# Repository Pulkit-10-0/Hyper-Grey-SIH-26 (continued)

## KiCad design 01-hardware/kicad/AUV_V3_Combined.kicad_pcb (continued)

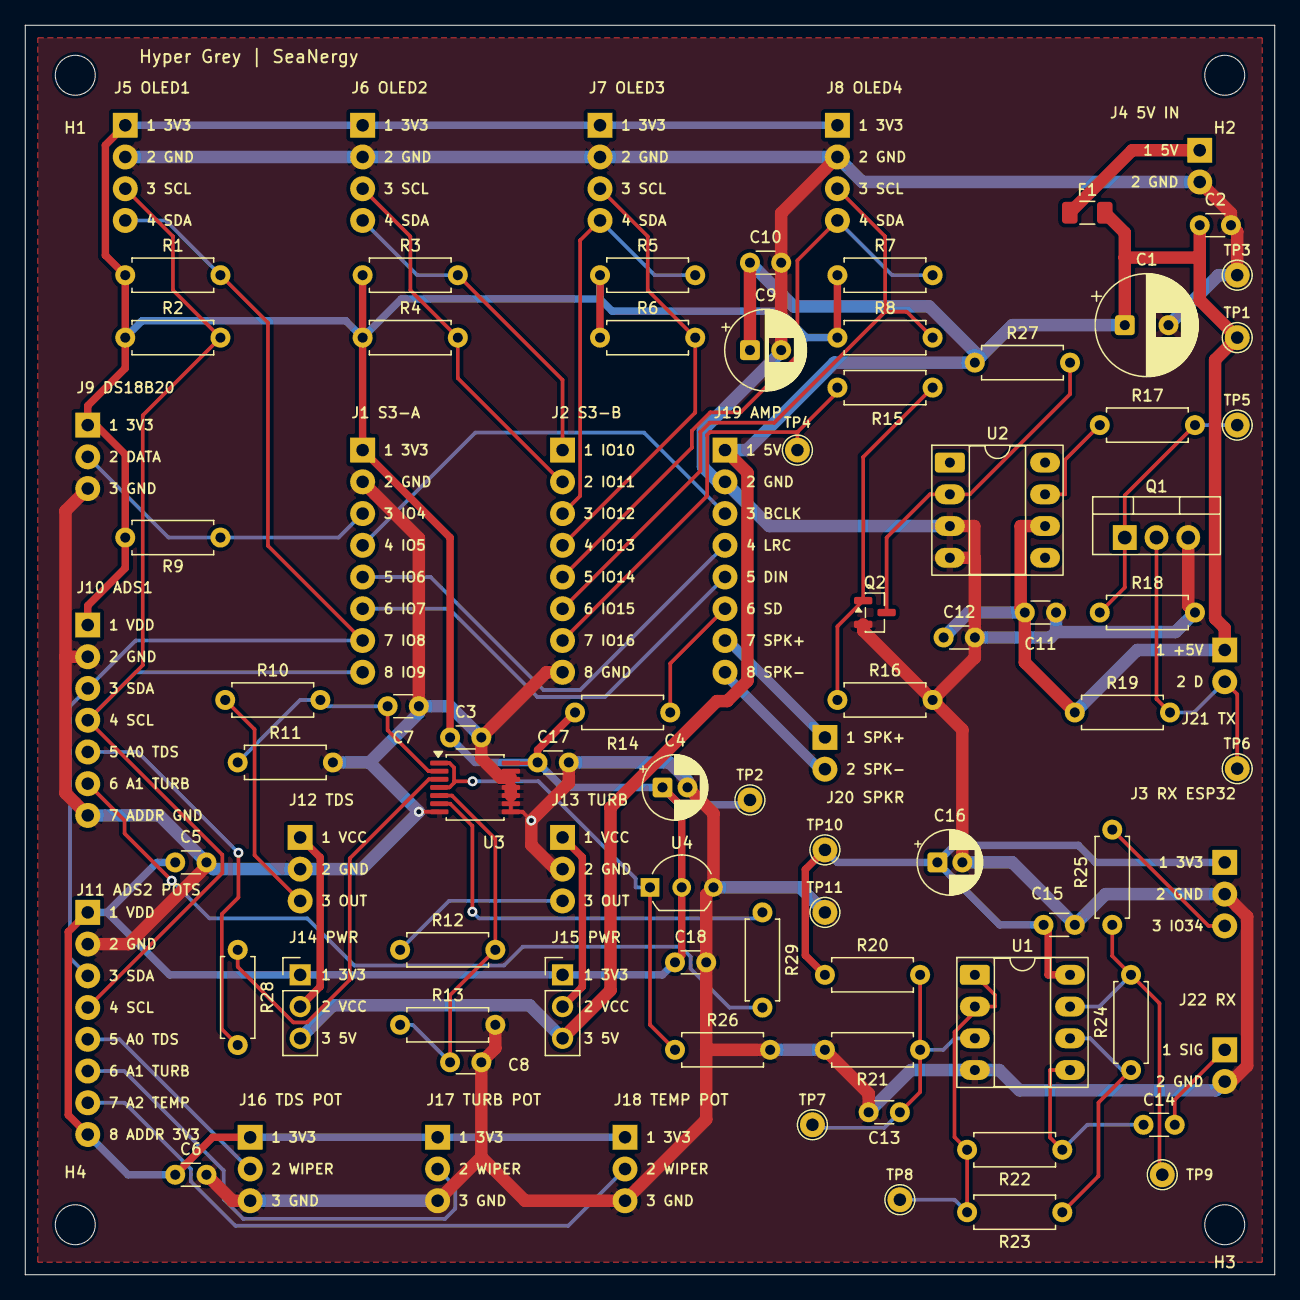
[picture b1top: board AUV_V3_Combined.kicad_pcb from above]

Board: 2 copper layers, 100.0 x 100.0 mm, 91 parts (0 on the bottom side), 47 nets.

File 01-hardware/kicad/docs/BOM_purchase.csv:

Quantity,References,Value,Footprint,Manufacturer part / selection,Assembly status
1,C1,470uF 10V,Capacitor_THT:CP_Radial_D8.0mm_P3.50mm,"470 uF >=10 V, diameter <=8 mm, pitch 3.5 mm",Fit
13,C2 C3 C5 C6 C7 C8 C10 C11 C13 C14 C15 C17 C18,100nF,Capacitor_THT:C_Disc_D3.0mm_W1.6mm_P2.50mm,"Nonpolar ceramic, >=10 V; match footprint body and 2.50 mm lead pitch",Fit
2,C4 C16,10uF 10V,Capacitor_THT:CP_Radial_D5.0mm_P2.00mm,"Polarized radial electrolytic, >=10 V; match footprint diameter and lead pitch",Fit
1,C9,100uF 10V,Capacitor_THT:CP_Radial_D6.3mm_P2.50mm,"Polarized radial electrolytic, >=10 V; match footprint diameter and lead pitch",Fit
1,C12,1uF,Capacitor_THT:C_Disc_D3.0mm_W1.6mm_P2.50mm,"Nonpolar ceramic, >=10 V; match footprint body and 2.50 mm lead pitch",Fit
1,F1,1A FUSE,Fuse:Fuse_1206_3216Metric,Littelfuse 0466001.NR,Fit
1,J14,TDS_VCC SELECT,Connector_PinHeader_2.54mm:PinHeader_1x03_P2.54mm_Vertical,2.54 mm pitch 1x3 male header + one removable 1x2 shunt,Fit 1x3 header; leave shunt OFF until sensor voltage is confirmed
1,J15,TURB_VCC SELECT,Connector_PinHeader_2.54mm:PinHeader_1x03_P2.54mm_Vertical,2.54 mm pitch 1x3 male header + one removable 1x2 shunt,Fit 1x3 header; leave shunt OFF until sensor voltage is confirmed
1,Q1,IRLZ44NPBF,Package_TO_SOT_THT:TO-220-3_Vertical,IRLZ44NPBF,Fit
1,Q2,AO3400A,Package_TO_SOT_SMD:SOT-23,AO3400A,Fit
8,R1 R2 R3 R4 R5 R6 R7 R8,4.7k DNP,Resistor_THT:R_Axial_DIN0207_L6.3mm_D2.5mm_P7.62mm_Horizontal,"Axial 0.25 W, 1% preferred, body <=6.3 x 2.5 mm, 7.62 mm lead pitch",DNP initially; fit only if this bus lacks suitable module pull-ups
2,R9 R27,4.7k,Resistor_THT:R_Axial_DIN0207_L6.3mm_D2.5mm_P7.62mm_Horizontal,"Axial 0.25 W, 1% preferred, body <=6.3 x 2.5 mm, 7.62 mm lead pitch",Fit
6,R10 R11 R12 R13 R20 R21,10k 1%,Resistor_THT:R_Axial_DIN0207_L6.3mm_D2.5mm_P7.62mm_Horizontal,"Axial 0.25 W, 1% preferred, body <=6.3 x 2.5 mm, 7.62 mm lead pitch",Fit
1,R14,2.2k,Resistor_THT:R_Axial_DIN0207_L6.3mm_D2.5mm_P7.62mm_Horizontal,"Axial 0.25 W, 1% preferred, body <=6.3 x 2.5 mm, 7.62 mm lead pitch",Fit
3,R15 R17 R25,100,Resistor_THT:R_Axial_DIN0207_L6.3mm_D2.5mm_P7.62mm_Horizontal,"Axial 0.25 W, 1% preferred, body <=6.3 x 2.5 mm, 7.62 mm lead pitch",Fit
2,R16 R26,100k,Resistor_THT:R_Axial_DIN0207_L6.3mm_D2.5mm_P7.62mm_Horizontal,"Axial 0.25 W, 1% preferred, body <=6.3 x 2.5 mm, 7.62 mm lead pitch",Fit
2,R18 R22,10k,Resistor_THT:R_Axial_DIN0207_L6.3mm_D2.5mm_P7.62mm_Horizontal,"Axial 0.25 W, 1% preferred, body <=6.3 x 2.5 mm, 7.62 mm lead pitch",Fit
1,R19,1k 0.25W,Resistor_THT:R_Axial_DIN0207_L6.3mm_D2.5mm_P7.62mm_Horizontal,"Axial 0.25 W, 1% preferred, body <=6.3 x 2.5 mm, 7.62 mm lead pitch",Fit
1,R23,1k 1%,Resistor_THT:R_Axial_DIN0207_L6.3mm_D2.5mm_P7.62mm_Horizontal,"Axial 0.25 W, 1% preferred, body <=6.3 x 2.5 mm, 7.62 mm lead pitch",Fit
1,R24,22k 1%,Resistor_THT:R_Axial_DIN0207_L6.3mm_D2.5mm_P7.62mm_Horizontal,"Axial 0.25 W, 1% preferred, body <=6.3 x 2.5 mm, 7.62 mm lead pitch",Fit
2,R28 R29,1k,Resistor_THT:R_Axial_DIN0207_L6.3mm_D2.5mm_P7.62mm_Horizontal,"Axial 0.25 W, 1% preferred, body <=6.3 x 2.5 mm, 7.62 mm lead pitch",Fit
1,U1,MCP6002-I/P,Package_DIP:DIP-8_W7.62mm_Socket_LongPads,MCP6002-I/P,Fit
1,U2,TC4426AEPA,Package_DIP:DIP-8_W7.62mm_Socket_LongPads,TC4426AEPA,Fit
1,U3,TMUX1511PWR,Package_SO:TSSOP-14_4.4x5mm_P0.65mm,TMUX1511PWR,Fit
1,U4,MCP100-315DI/TO,Package_TO_SOT_THT:TO-92_Inline_Wide,MCP100-315DI/TO,Fit

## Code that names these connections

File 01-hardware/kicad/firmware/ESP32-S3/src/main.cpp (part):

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// MAX98357A
// ------------------------------------------------------------

#define I2S_BCLK_PIN 5
#define I2S_LRC_PIN  6
#define I2S_DIN_PIN  7


// ------------------------------------------------------------
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

    Serial.println();
    Serial.println("40 kHz ultrasonic TX active on GPIO16.");
    Serial.println();


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

    I2S.setPins(
        I2S_BCLK_PIN,
        I2S_LRC_PIN,
        I2S_DIN_PIN
    );


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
